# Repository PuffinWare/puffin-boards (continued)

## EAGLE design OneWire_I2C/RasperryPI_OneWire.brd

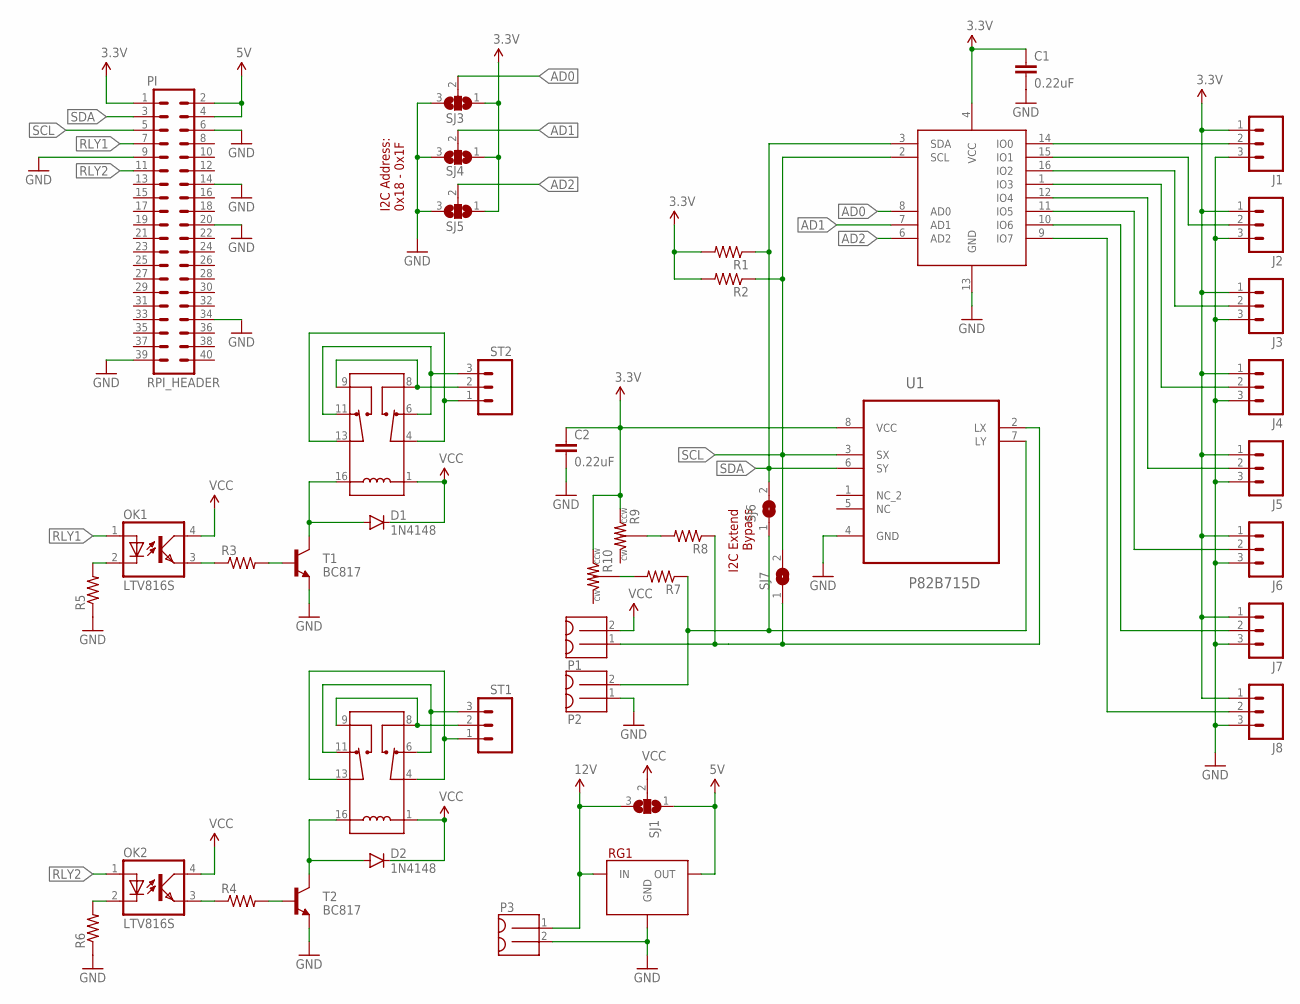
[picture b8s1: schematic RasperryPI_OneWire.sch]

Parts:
C1, C2: 0.22uF; 0603-CAP
D1, D2: 1N4148; DIODE-1N4148
J1, J2, J3, J4, J5, J6, J7, J8: M03PTH; 1X03
OK1, OK2: LTV816S; SMD4
P1, P2, P3: MOLEX_MINILITE_TRAP_2
PI: RPI_HEADER
R1, R2, R3, R4, R5, R6, R7, R8: RESISTOR0805-RES; 0805
R9, R10: POT_3MM
RG1: MURATA_REG; MURATA_REG_HOR
RLY1, RLY2: HK19F_5V_DPDT_RELAY; DIP16-RELAY
SJ1, SJ3, SJ4, SJ5: SJ2W; SJ_2
SJ6, SJ7: SJ
ST1, ST2: SCREWTERM_3; SCREWTERM_0.2X3
T1, T2: BC817; SOT-23
U1: P82B715D; SOIC127P600X175-8N
U2: DS2482-800; SOIC16

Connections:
3.3V: C1.1, C2.1, J1.1, J2.1, J3.1, J4.1, J5.1, J6.1, J7.1, J8.1, PI.1, R1.2, R2.2, R9.1, R10.1, SJ3.1, SJ4.1, SJ5.1, U1.8 (VCC), U2.4 (VCC)
5V: PI.2, PI.4, RG1.3 (OUT), SJ1.1
12V: P3.1, RG1.1 (IN), SJ1.3
AD0: SJ3.2, U2.8 (AD0)
AD1: SJ4.2, U2.7 (AD1)
AD2: SJ5.2, U2.6 (AD2)
GND: C1.2, C2.2, J1.3, J2.3, J3.3, J4.3, J5.3, J6.3, J7.3, J8.3, P2.1, P3.2, PI.6, PI.9, PI.14, PI.20, PI.34, PI.39, R5.1, R6.1, RG1.2 (GND), SJ3.3, SJ4.3, SJ5.3, T1.2 (E), T2.2 (E), U1.4 (GND), U2.13 (GND)
LCL: P1.1, R8.1, SJ7.1, U1.2 (LX)
LDA: P2.2, R7.1, SJ6.1, U1.7 (LY)
unnamed: J1.2, U2.14 (IO0)
unnamed: J2.2, U2.15 (IO1)
unnamed: J3.2, U2.16 (IO2)
unnamed: J4.2, U2.1 (IO3)
unnamed: J5.2, U2.12 (IO4)
unnamed: J6.2, U2.11 (IO5)
unnamed: J7.2, U2.10 (IO6)
unnamed: J8.2, U2.9 (IO7)
unnamed: OK2.3 (EMIT), R4.1
unnamed: R4.2, T2.1 (B)
unnamed: D2.A, RLY2.16 (L2), T2.3 (C)
unnamed: D1.A, RLY1.16 (L2), T1.3 (C)
unnamed: R3.2, T1.1 (B)
unnamed: OK1.3 (EMIT), R3.1
unnamed: RLY2.4 (C1), RLY2.13 (C2), ST1.1
unnamed: RLY2.6 (NC1), RLY2.11 (NC2), ST1.3
unnamed: RLY2.8 (NO1), RLY2.9 (NO2), ST1.2
unnamed: RLY1.4 (C1), RLY1.13 (C2), ST2.1
unnamed: RLY1.6 (NC1), RLY1.11 (NC2), ST2.3
unnamed: RLY1.8 (NO1), RLY1.9 (NO2), ST2.2
unnamed: OK1.2 (C), R5.2
unnamed: OK2.2 (C), R6.2
unnamed: R7.2, R10.2
unnamed: R8.2, R9.2
RLY1: OK1.1 (A), PI.7
RLY2: OK2.1 (A), PI.11
SCL: PI.5, R2.1, SJ7.2, U1.3 (SX), U2.2 (SCL)
SDA: PI.3, R1.1, SJ6.2, U1.6 (SY), U2.3 (SDA)
VCC: D1.C, D2.C, OK1.4 (COL), OK2.4 (COL), P1.2, RLY1.1 (L1), RLY2.1 (L1), SJ1.2

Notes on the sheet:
I2C Address: 0x18 - 0x1F
I2C Extend Bypass

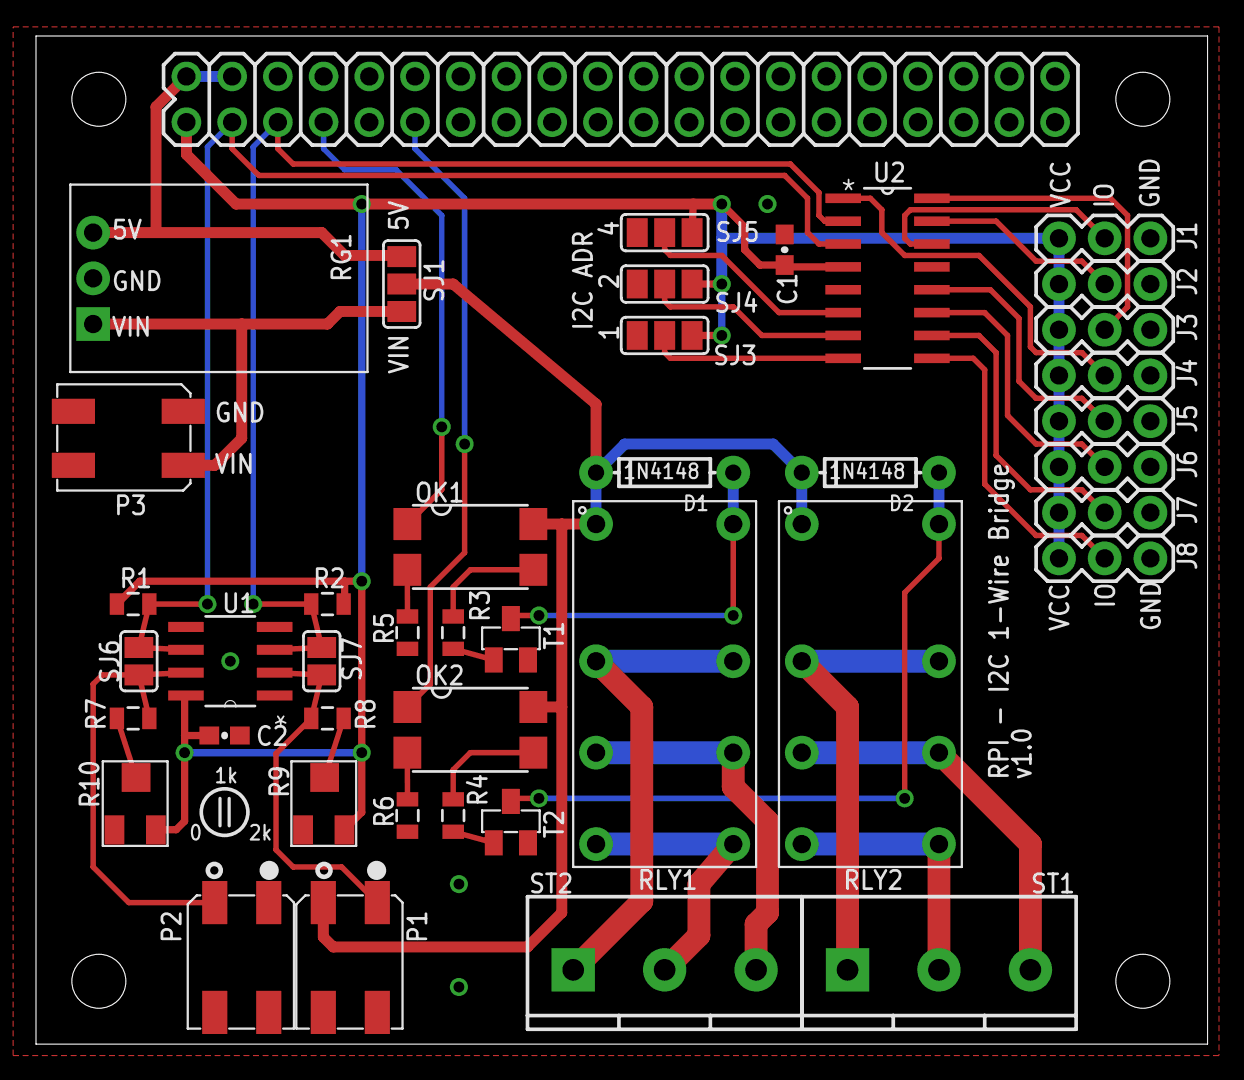
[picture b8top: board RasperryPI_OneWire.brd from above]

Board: 2 copper layers, 65.1 x 56.0 mm, 44 parts (0 on the bottom side), 38 nets.

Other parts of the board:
U$6: RPI_BOARD

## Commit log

2016-02-06 First version of OneWire to I2C bridge
2016-02-06 Added Schematic and board for DS2482-800
2016-02-08 Tweaks to I2C 1Wire bridge boards
2016-02-08 Changed I2C pullup jumpers to single 3-way jumper
2016-02-09 Added extra screw terminals on I2C side
2016-02-10 Added CellarRemote board and components
2016-02-14 Added CellarRemote_I2CExt
2016-02-14 Added 8 port OneWire I2C bridge with Extender
2016-02-14 Added Raspberry Pi 8 Port OneWire board
2016-02-16 Added Raspberry pi board, updated I2C extender pullup resistors to other boards
2016-02-18 Tweaks to cellar remote board
2016-02-18 Ver 2 of CellarRemote with I2C extender
2016-02-18 WIP - First attempt at reg board
2016-02-19 V1.0 initial design complete of Regulator board
2016-02-19 Added labels to pins on reg board
2016-02-19 Added molex minilite connector
2016-03-10 Minor updates to CellarRemote
2016-03-10 Added lots of new components
2016-03-10 Updates to v1 of reg_i2c. New ext_i2c
2016-03-11 First cut at CellarControl board
2016-03-12 Completed Cellar Controller
2016-03-16 Finished RPI 1Wire board
2016-03-16 Minor changes to cellar controller. Rework of ext_i2c board
2016-04-14 Standardized i2c connections, fixed 1Wire connections, lots of cleanup
2016-04-14 Enlarged board, added regulator, replaced header with push connectors
2016-04-16 Change reg_i2c to use a 2x8 header
2017-09-21 Add gate boards
2017-09-28 Fix gate3 relay and ps orientation
2017-10-02 Gate 4, and misc updates
2017-10-16 Update gate4, new gate5 with eseries
2018-02-01 Gate 5 updated, not sure what changed
2018-02-01 Added gate6, which is actually v1.0
2018-02-01 Clean up old files, move gate6 to gate
2018-02-04 Gate to 2 relays and enclosure fit
2018-02-05 Gate: Fix ext header, move pwr led. misc cleanup.
2022-12-19 Reclaim on garage board, add boron,argon board
2023-01-15 New argon and feather boards
2023-01-15 Minor updates to argon/feather
